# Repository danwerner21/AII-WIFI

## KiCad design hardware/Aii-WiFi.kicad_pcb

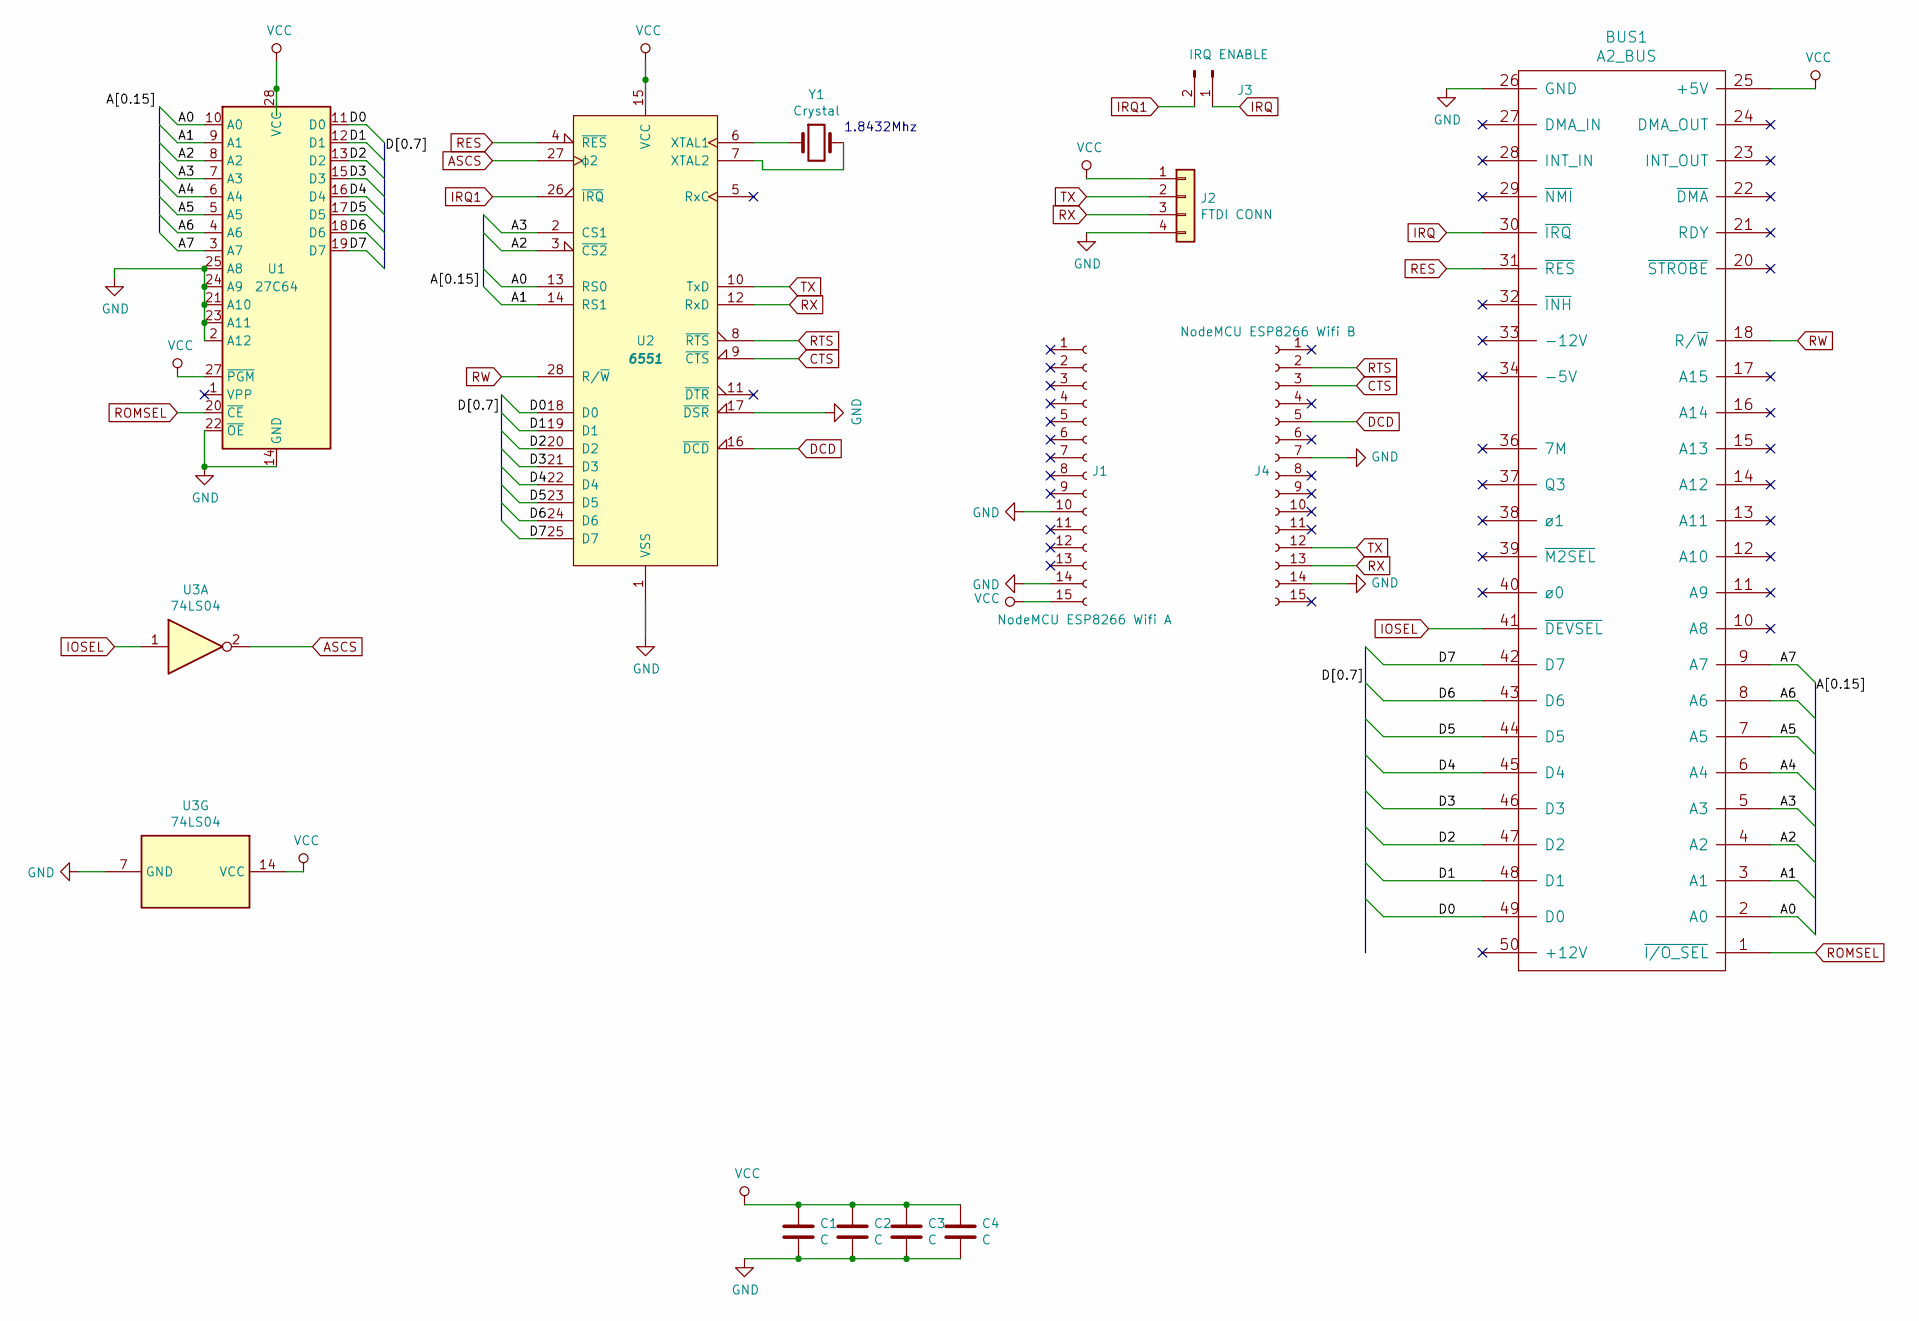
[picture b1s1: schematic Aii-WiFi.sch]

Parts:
BUS1: A2_BUS; BUS_A2
C1, C2, C3, C4: C; C_Rect_L7.0mm_W2.0mm_P5.00mm
J1: NodeMCU ESP8266 Wifi A; PinHeader_1x15_P2.54mm_Vertical
J2: FTDI CONN; PinHeader_1x04_P2.54mm_Vertical
J3: IRQ ENABLE; PinSocket_1x02_P2.54mm_Vertical
J4: NodeMCU ESP8266 Wifi B; PinHeader_1x15_P2.54mm_Vertical
U1: 27C64; DIP-28_W15.24mm_Socket
U2: 6551; DIP-28_W15.24mm_Socket
U3: 74LS04; DIP-14_W7.62mm_Socket
Y1: Crystal; Crystal_HC52-8mm_Vertical

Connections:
/A0: BUS1.2 (A0), U1.10 (A0), U2.13 (RS0)
/A1: BUS1.3 (A1), U1.9 (A1), U2.14 (RS1)
/A2: BUS1.4 (A2), U1.8 (A2), U2.3 (~CS2)
/A3: BUS1.5 (A3), U1.7 (A3), U2.2 (CS1)
/A4: BUS1.6 (A4), U1.6 (A4)
/A5: BUS1.7 (A5), U1.5 (A5)
/A6: BUS1.8 (A6), U1.4 (A6)
/A7: BUS1.9 (A7), U1.3 (A7)
/D0: BUS1.49 (D0), U1.11 (D0), U2.18 (D0)
/D1: BUS1.48 (D1), U1.12 (D1), U2.19 (D1)
/D2: BUS1.47 (D2), U1.13 (D2), U2.20 (D2)
/D3: BUS1.46 (D3), U1.15 (D3), U2.21 (D3)
/D4: BUS1.45 (D4), U1.16 (D4), U2.22 (D4)
/D5: BUS1.44 (D5), U1.17 (D5), U2.23 (D5)
/D6: BUS1.43 (D6), U1.18 (D6), U2.24 (D6)
/D7: BUS1.42 (D7), U1.19 (D7), U2.25 (D7)
ASCS: U2.27 (ϕ2), U3.2
CTS: J4.3, U2.9 (~CTS)
DCD: J4.5, U2.16 (~DCD)
GND: BUS1.26 (GND), C1.2, C2.2, C3.2, C4.2, J1.10, J1.14, J2.4, J4.7, J4.14, U1.2 (A12), U1.14 (GND), U1.21 (A10), U1.22 (~OE), U1.23 (A11), U1.24 (A9), U1.25 (A8), U2.1 (VSS), U2.17 (~DSR), U3.7 (GND)
IOSEL: BUS1.41 (~DEVSEL), U3.1
IRQ: BUS1.30 (~IRQ), J3.1
IRQ1: J3.2, U2.26 (~IRQ)
unnamed: U2.6 (XTAL1), Y1.1
unnamed: U2.7 (XTAL2), Y1.2
RES: BUS1.31 (~RES), U2.4 (~RES)
ROMSEL: BUS1.1 (~I/O_SEL), U1.20 (~CE)
RTS: J4.2, U2.8 (~RTS)
RW: BUS1.18 (R/~W), U2.28 (R/~W)
RX: J2.3, J4.13, U2.12 (RxD)
TX: J2.2, J4.12, U2.10 (TxD)
VCC: BUS1.25 (+5V), C1.1, C2.1, C3.1, C4.1, J1.15, J2.1, U1.27 (~PGM), U1.28 (VCC), U2.15 (VCC), U3.14 (VCC)

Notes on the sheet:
1.8432Mhz

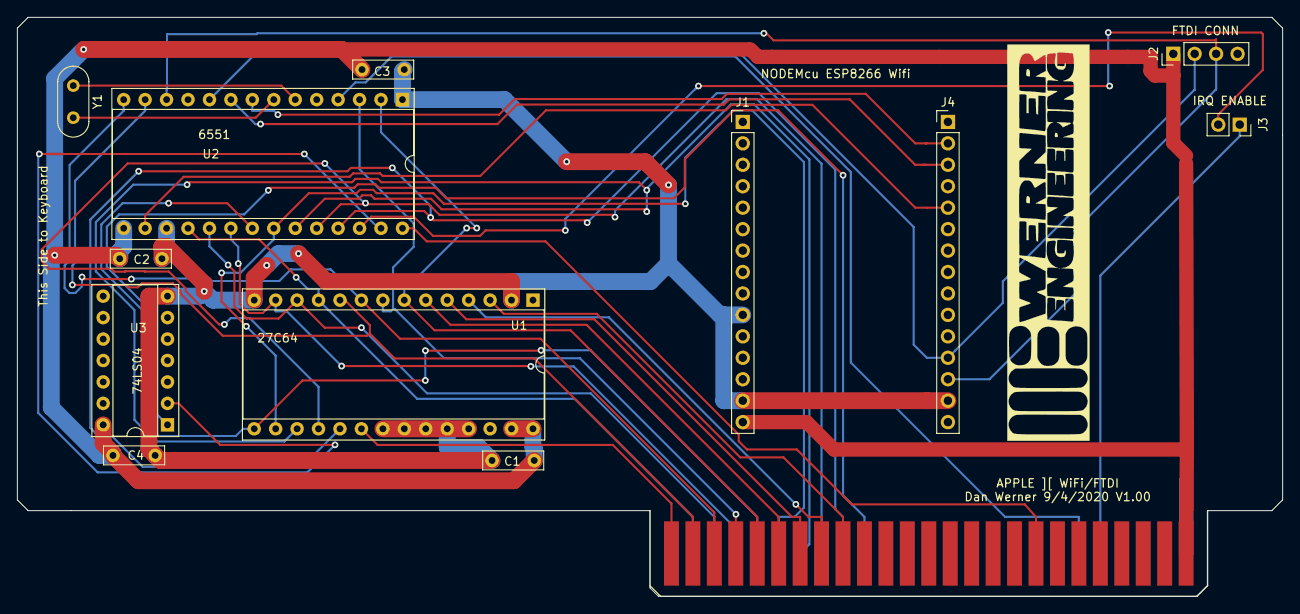
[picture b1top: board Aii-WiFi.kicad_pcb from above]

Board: 2 copper layers, 149.9 x 68.6 mm, 13 parts (0 on the bottom side), 32 nets.
